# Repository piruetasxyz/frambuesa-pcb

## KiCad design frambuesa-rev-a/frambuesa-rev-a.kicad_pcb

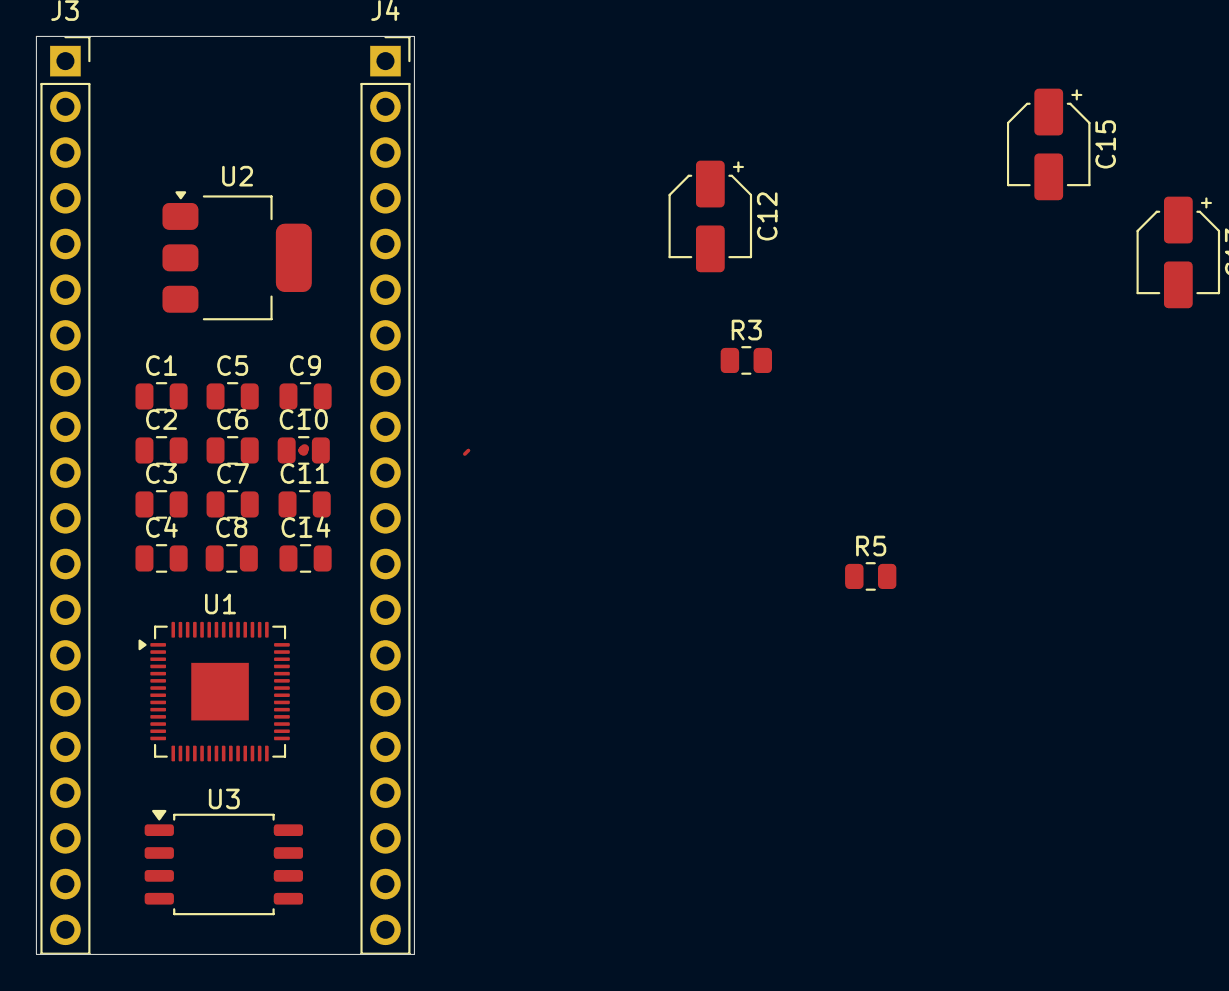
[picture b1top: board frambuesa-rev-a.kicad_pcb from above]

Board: 2 copper layers, 21.0 x 51.0 mm, 22 parts (0 on the bottom side), 30 nets.

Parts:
C1, C9: 1u; C_0805_2012Metric
C2, C3, C4, C5, C6, C7, C8, C10, C11, C14: 100n; C_0805_2012Metric
C12, C13, C15: 10u; CP_Elec_4x5.4
J3, J4: Conn_02x18_Odd_Even; PinSocket_1x20_P2.54mm_Vertical
R3: 1k; R_0805_2012Metric
R5: 1K; R_0805_2012Metric
U1: RP2040; QFN-56-1EP_7x7mm_P0.4mm_EP3.2x3.2mm
U2: NCP1117-3.3_SOT223; SOT-223-3_TabPin2
U3: W25Q128JVS; SOIC-8_5.3x5.3mm_P1.27mm

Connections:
+1V1: C9.1, C10.1, C11.1, U1.23 (DVDD), U1.45 (VREG_VOUT), U1.50 (DVDD)
+3V3: C1.1, C2.1, C3.1, C4.1, C5.1, C6.1, C7.1, C8.1, C13.1, C14.1, C15.1, J3.2, U1.1 (IOVDD), U1.10 (IOVDD), U1.22 (IOVDD), U1.33 (IOVDD), U1.42 (IOVDD), U1.43 (ADC_AVDD), U1.44 (VREG_VIN), U1.48 (USB_VDD), U1.49 (IOVDD), U2.2 (VO), U3.8 (VCC)
/GPIO00: J3.4, U1.2 (GPIO0)
/GPIO01: J3.6, U1.3 (GPIO1)
/GPIO02: J3.8, U1.4 (GPIO2)
/GPIO03: J3.10, U1.5 (GPIO3)
/GPIO04: J3.12, U1.6 (GPIO4)
/GPIO05: J3.14, U1.7 (GPIO5)
/GPIO06: J3.16, U1.8 (GPIO6)
/GPIO07: J3.18, U1.9 (GPIO7)
/GPIO08: J3.20, U1.11 (GPIO8)
/GPIO20: J4.19, U1.31 (GPIO20)
/GPIO21: J4.17, U1.32 (GPIO21)
/GPIO22: J4.15, U1.34 (GPIO22)
/GPIO23: J4.13, U1.35 (GPIO23)
/GPIO24: J4.11, U1.36 (GPIO24)
/GPIO25: J4.9, U1.37 (GPIO25)
/GPIO26_ADC0: J4.7, U1.38 (GPIO26/ADC0)
/GPIO27_ADC1: J4.5, U1.39 (GPIO27/ADC1)
/GPIO28_ADC2: J4.3, U1.40 (GPIO28/ADC2)
/GPIO29_ADC3: J4.1, U1.41 (GPIO29/ADC3)
/NOT_QSPI_SS: R3.2, U1.56 (~QSPI_SS), U3.1 (~CS)
/QSPI_SCLK: U1.52 (QSPI_SCLK), U3.6 (CLK)
/QSPI_SD0: U1.53 (QSPI_SD0), U3.5 (DI/IO_{0})
/QSPI_SD1: U1.55 (QSPI_SD1), U3.2 (DO/IO_{1})
/QSPI_SD2: U1.54 (QSPI_SD2), U3.3 (~WP/IO_{2})
/QSPI_SD3: U1.51 (QSPI_SD3), U3.7 (~HOLD/~RESET/IO_{3})
/XOUT: R5.2, U1.21 (XOUT)
GND: C1.2, C2.2, C3.2, C4.2, C5.2, C6.2, C7.2, C8.2, C9.2, C10.2, C11.2, C12.2, C13.2, C14.2, C15.2, J3.1, J3.3, J3.5, J3.7, J3.9, J3.11, J3.13, J3.15, J3.17, J3.19, J4.2, J4.4, J4.6, J4.8, J4.10, J4.12, J4.14, J4.16, J4.18, J4.20, U1.19 (TESTEN), U1.57 (GND), U2.1 (GND), U3.4 (GND)
VBUS: C12.1, U2.3 (VI)
